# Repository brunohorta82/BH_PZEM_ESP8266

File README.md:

# BH PZEM

**Conteúdo **   
1. [Intro](#id1)
2. [Hardware](#id2)
3. [Firmware](https://github.com/brunohorta82/BH-Easy-Iot)
4. [Hack de sentido da corrente](#id4)
5. [Exemplos](#id5)
   - [BH PZEM-004 Wi-Fi](#id6)
5. [Donativos](#id7)

## Intro 

**BH Pzem** é um dispositivo baseado em ESP8266 e PZEM-004 que mede energia e / ou temperatura e enviaos dados a um broker MQTT e / ou Emoncms. O BH Pzem é modular, o que significa que podemos começar com um simples módulo de energia até um sistema de monitorização de produção energética, juntamente com detecção de temperatura (até 10 sensores de temperatura digital). Podemos ainda adicionar um diplay Oled e relés.
Os dados são enviados via Wi-Fi

**Painel de Controlo:**

**Medição de Energia:**
  - Baseado no PZEM-004
  - Leituras muito rigorosas 
  - Possibilidade de detecão de sentido de energia 
  - Voltagem, Amperagem, Potência, Energia

**Medição de Temperatura:**
  - Baseado no sensor 1-wire DS18B20
  - Permite adicionar até 10 sensores digitais DS18B20
  - Endereços dos sensores geridos na interface Web

**Relé :**
  - Controlado via MQTT

**ESP8266**:
  - Facilmente configurado na Interface Web
  - Envio dos dados em JSON via MQTT
  - Envio dos dados para um servidor Emoncms local/remoto
  
## Hardware 

Qtd | Item | Imagem
:---: | :---: | ---:
1 | PZEM-004 | `...`
1 | ESP-12E | `...`
1 | PCB BH-PZEM Wi-Fi | `...`
1 | Fonte HLK-PM01 | `...`
1 | Regulador de Tensão AMS1117 3.3v | `...`
1 | Condensador Cerâmico 100nF SMD | `...`
5 | Resistência 10K 0603 | `...`
1 | Resistência 4.7K 0603 | `...`
1 | Resistência 1K 0603 | `...`
1 | Optocopolador PC | `...`
2 | Botão 3*4*2 MM SMD | `...`
1 | Fusível T2A 2A 250 | `...`
1 | Sensor temperatua DS18B20 | `...`
1 | Terminal de Parafuso 2P 5.0mm  | `...`
2 | Terminal 2P 2.54mm  | `...`
1 | Conector de 9 Pinos Fêmea 2.54mm | `...`
1 | Conector de 8 Pinos Fêmea 2.54mm | `...`
1 | Conector de 4 Pinos Macho 2.54mm | `...`
1 | Conector de 7 Pinos Macho 2.54mm | `...`

## Software 

- Arduino Ide
- Editar o ficheiro config.h com o setup inicial
- Upload do Firmware para o ESP8266
- Aceder ao AP `SSID:BH_PZEM_NODE_ID` e configurar a Rede Wi-Fi
- Navegar até  `http://<bh-pzem name>.local` ou `http://<bh-pzem IP address>`
- Verificar o sentido da corrente caso tenham feito o Hack para a deteção
- Configurar o `MQTT broker` e/ou a conta do `Emoncms` 
- E tá feito, agora é só curtir :) 

## Hack para deteção de sentido de corrente 

![](https://lh3.googleusercontent.com/7oKvPvdqY3lP6zBprZ33XxJ7tKCSPjcxN2w-OqwHl_1SzNu80wvdnXQUsuom1qUd44zljcSAKoW6R_QD6Fw6dyNdrQpZGyCAt7fK76CRAaeEPu2qT8z-xMeqMLAlgMNtwaDBF7miqPXhsgoQ-rWaterlj8KB61w-i8nbBX3sqG_NviRIJFRPZu4y5Mk5QQHA83q366xY_NipzpD8CfSDKwin57H3Htds_hMZ-07q1bP9mxqiQBRQqcq6nFyu7SyfzQPI7FPg7txX6qM7KTZdOb53coQP14PXP9ZpZgZd6tcLpuRveteLxfdhUHiUXz74R1f_4OeA_25O--yq3BcZT_W89wb5o-ZRAX4VKxyWw7SOmyMhGib1QK7HJxYOTOWC5yf9IasuEWV_vbtsjChd_gD7Al2RD4akmTF-P8RQy6oLgGEKNINEdbHCTc4NhU0PtUVe3b90hhll2i0vlXHoQQ_Dcv1H4UQkiork0te3gWIpN9IEScdoKep3nyKpx4NwDmuup3uilXumtjUWld5qL1ifNlgKCKj39EcPMyswWAbB7pGrEsRqt0L_xvEW9gpEuPkjH6MUEL-biGVslIl6hkCvgLHb1iIcVd2EOjmNMurGXLUkB2KS3h3Vw4LIQRWzvFUrmJfLbP9hZKorvSnoDPO2MfHhwYYeXgx2m2J11w=w800-h402-no)

## Exemplos de BH-PZEM 

### BH PZEM-004 Wi-Fi 

## Caixas e Adaptadores
 - [BHPZEM Suporte DIN Powered by Bruno Horta](https://cad.onshape.com/documents/db83fdb5f2287efd0e4b6ae1/w/3f678a7db5145870a715b4d4/e/e8a96d2384c3348520138283)

## Donativos

Se gostas-te do projeto podes fazer o teu donativo :).

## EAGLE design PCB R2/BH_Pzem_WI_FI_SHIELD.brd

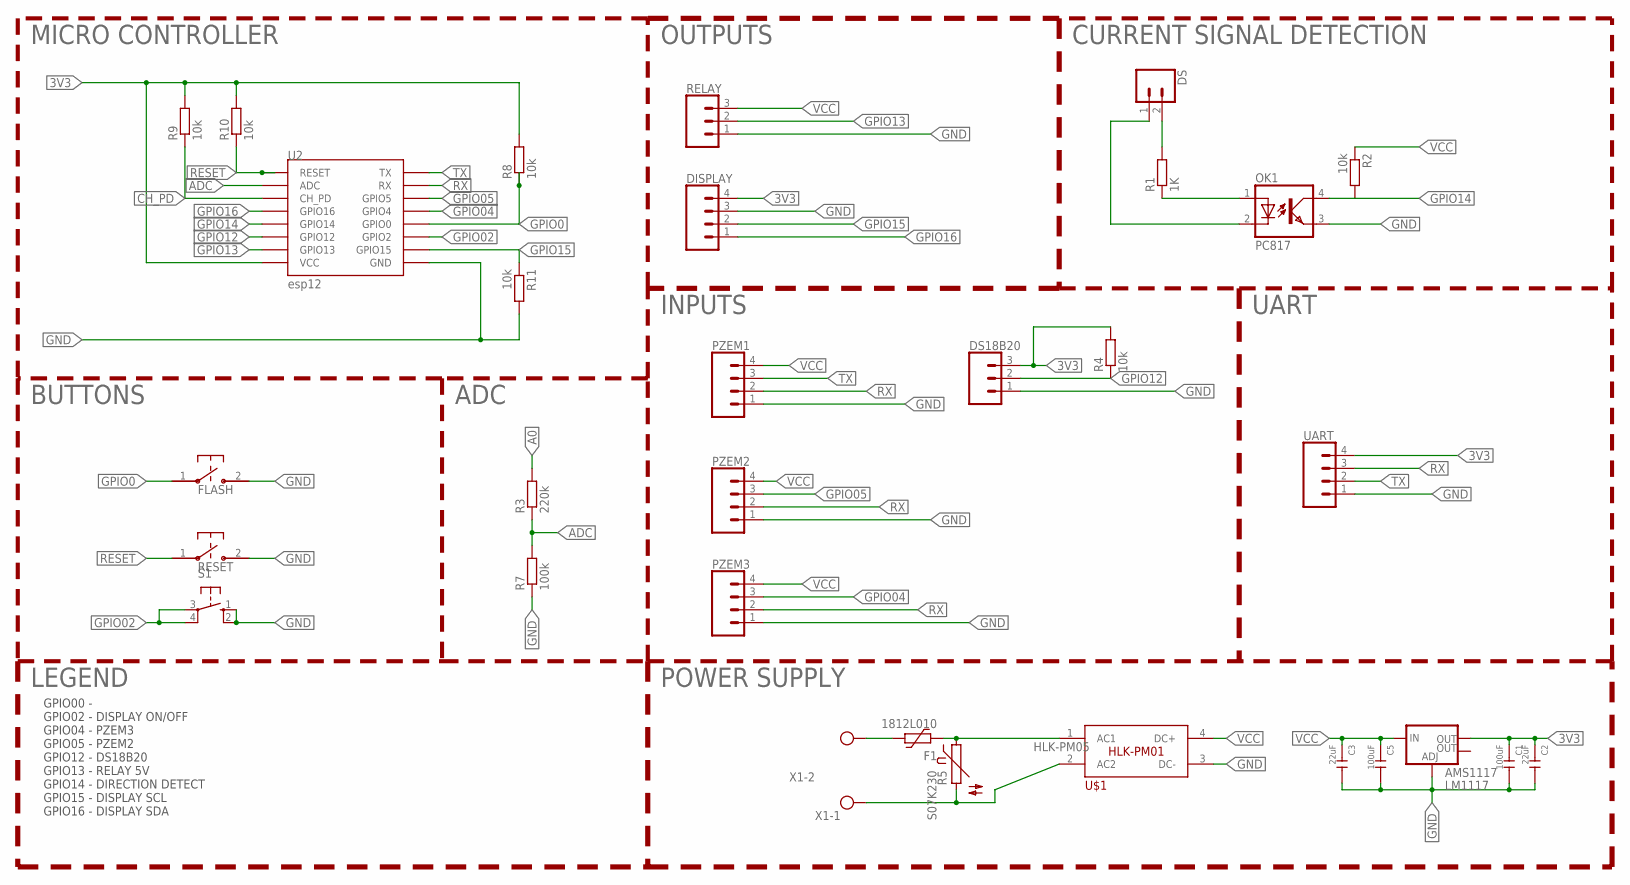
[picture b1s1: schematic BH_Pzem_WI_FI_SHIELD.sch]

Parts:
AMS1117: LM1117; SOT223
C1, C5: 100uF; C1206
C2, C3: 22uF; C1206
DISPLAY: CONN_04JST-PTH-VERT; JST-4-PTH-VERT
DS: CONN_02; 1X02
DS18B20: CONN_03JST-PTH-VERT; JST-3-PTH-VERT
F1: 1812L010; 1812L
FLASH: B3U-1000P-2P-SMD; B3U-1000P
OK1: PC817; DIL04
PZEM1, PZEM2, PZEM3: CONN_04JST-PTH-VERT; JST-4-PTH-VERT
R1: 1K; R0603
R2, R4, R8, R9, R10, R11: 10k; R0603
R3: 220k; R0603
R5: S07K230
R7: 100k; R0603
RELAY: CONN_03JST-PTH-VERT; JST-3-PTH-VERT
RESET: B3U-1000P-2P-SMD; B3U-1000P
S1: 10-XX; B3F-10XX
U2: esp12; ESP12-SMD
U$1: HLK-PM01
UART: CONN_04JST-PTH-VERT; JST-4-PTH-VERT
X1: W237-102

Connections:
3V3: AMS1117.2 (OUT), C1.1, C2.1, DISPLAY.4, DS18B20.3, R4.2, R8.2, R9.2, R10.2, U2.VCC, UART.4
A0: R3.2
ADC: R3.1, R7.2, U2.ADC
CH_PD: R9.1, U2.CH_PD
GND: AMS1117.1 (ADJ), C1.2, C2.2, C3.2, C5.2, DISPLAY.3, DS18B20.1, FLASH.2, OK1.3 (EMIT), PZEM1.1, PZEM2.1, PZEM3.1, R7.1, R11.2, RELAY.1, RESET.2, S1.1 (S), S1.2 (S1), U2.GND, U$1.3 (DC-), UART.1
GPIO0: FLASH.1, R8.1, U2.GPIO0
GPIO02: S1.3, S1.4 (P1), U2.GPIO2
GPIO04: PZEM3.3, U2.GPIO4
GPIO05: PZEM2.3, U2.GPIO5
GPIO12: DS18B20.2, R4.1, U2.GPIO12
GPIO13: RELAY.2, U2.GPIO13
GPIO14: OK1.4 (COL), R2.2, U2.GPIO14
GPIO15: DISPLAY.2, R11.1, U2.GPIO15
GPIO16: DISPLAY.1, U2.GPIO16
LINE_L: F1.2, R5.1, U$1.1 (AC1)
unnamed: OK1.1 (A), R1.1
unnamed: F1.1, X1.2
unnamed: DS.2, R1.2
NEUTRAL_IN: R5.2, U$1.2 (AC2), X1.1
RESET: R10.1, RESET.1, U2.RESET
RX: PZEM1.2, PZEM2.2, PZEM3.2, U2.RXD0 (RX), UART.3
SIGNAL_GND: DS.1, OK1.2 (C)
TX: PZEM1.3, U2.TXD0 (TX), UART.2
VCC: AMS1117.3 (IN), C3.1, C5.1, PZEM1.4, PZEM2.4, PZEM3.4, R2.1, RELAY.3, U$1.4 (DC+)

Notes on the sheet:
CURRENT SIGNAL DETECTION
INPUTS
BUTTONS
MICRO CONTROLLER
HLK-PM05
ADC
OUTPUTS
GPIO00 - GPIO02 - DISPLAY ON/OFF GPIO04 - PZEM3 GPIO05 - PZEM2 GPIO12 - DS18B20 GPIO13 - RELAY 5V GPIO14 - DIRECTION DETECT GPIO15 - DISPLAY SCL GPIO16 - DISPLAY SDA
POWER SUPPLY
LEGEND
UART

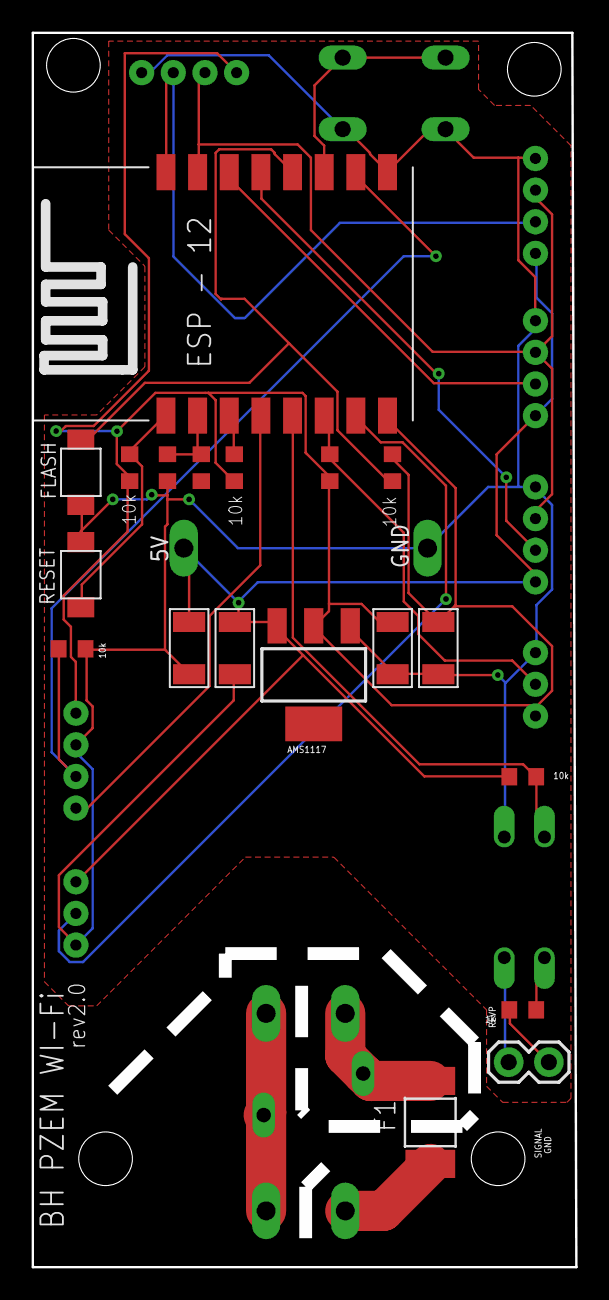
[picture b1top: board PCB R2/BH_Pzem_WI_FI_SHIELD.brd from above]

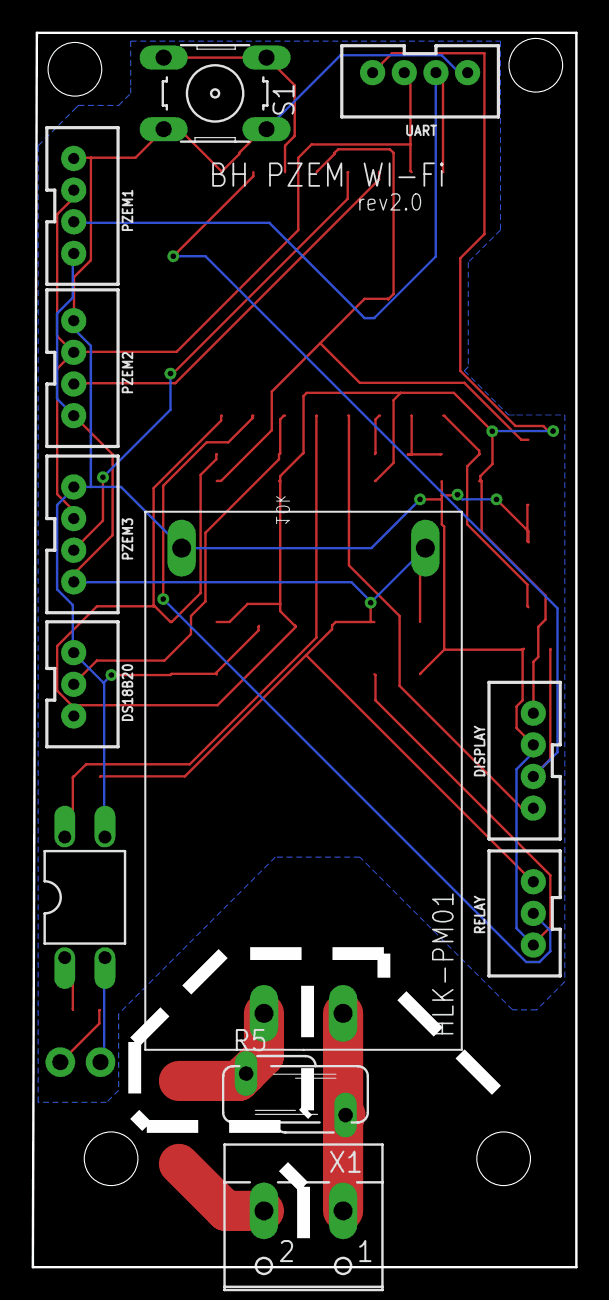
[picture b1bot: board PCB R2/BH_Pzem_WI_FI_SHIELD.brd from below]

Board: 2 copper layers, 33.7 x 77.3 mm, 31 parts (12 on the bottom side), 23 nets.

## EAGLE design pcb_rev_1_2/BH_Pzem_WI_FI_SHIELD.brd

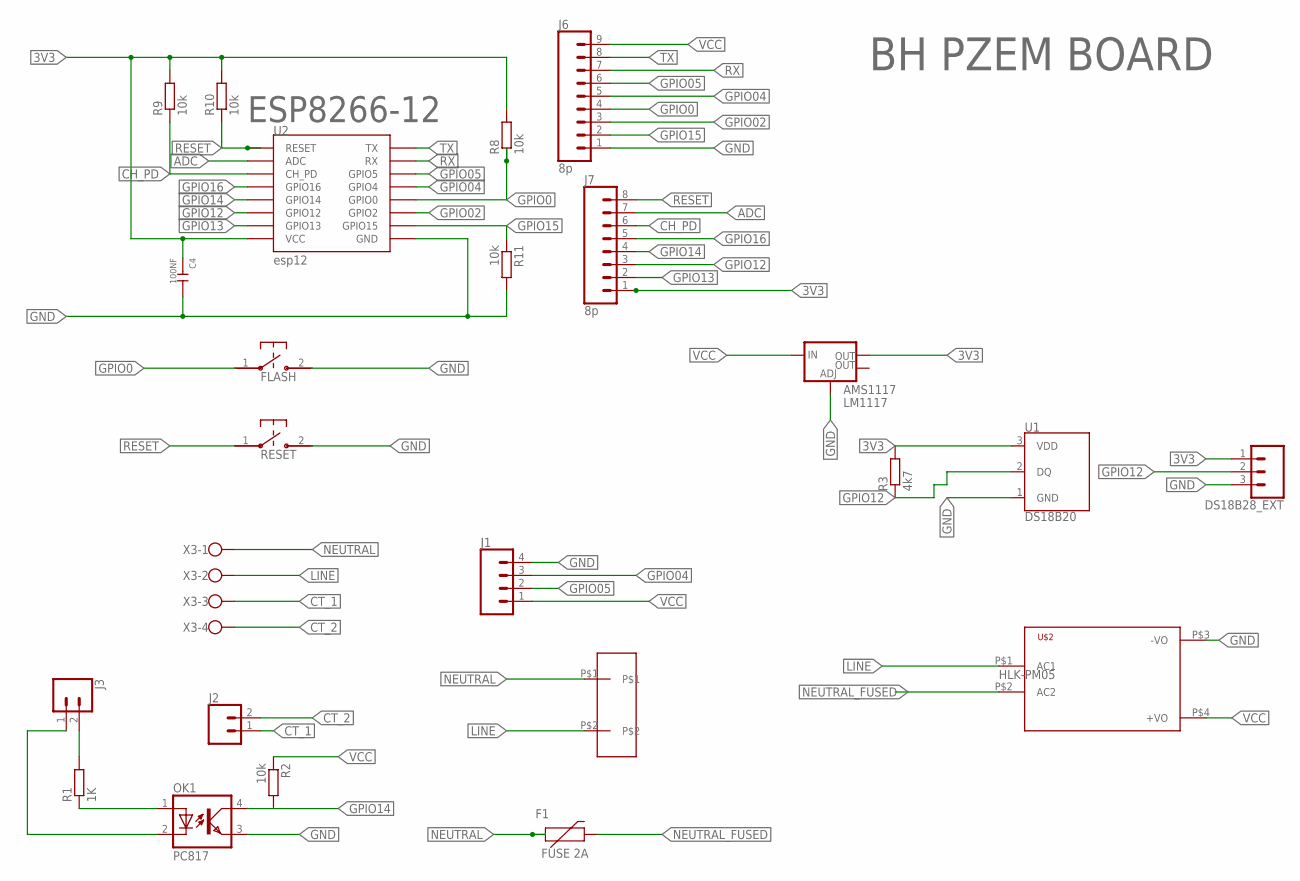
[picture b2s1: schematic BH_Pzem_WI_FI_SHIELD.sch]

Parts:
AMS1117: LM1117; SOT223
C4: 100NF; C1206
DS18B28_EXT: CONN_03; 1X03
F1: FUSE 2A; PTH
FLASH: B3U-1000P-2P-SMD; B3U-1000P
J1: CONN_04; 1X04
J2, J3: CONN_02; 1X02
J6: 8p; 1X09
J7: 8p; 1X08
OK1: PC817; DIL04
R1: 1K; R0603
R2, R8, R9, R10, R11: 10k; R0603
R3: 4k7; R0603
RESET: B3U-1000P-2P-SMD; B3U-1000P
U1: DS18B20; TO-92-AMMO
U2: esp12; ESP12-SMD
U$1: SCREWTERMINALS_5MM_2; TERMINAL_2X
U$2: HKLPM01
X3: W237-4

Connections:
3V3: AMS1117.2 (OUT), C4.1, DS18B28_EXT.1, J7.1, R3.2, R8.2, R9.2, R10.2, U1.3 (VDD), U2.VCC
ADC: J7.7, U2.ADC
CH_PD: J7.6, R9.1, U2.CH_PD
CT_1: J2.1, X3.3
CT_2: J2.2, X3.4
GND: AMS1117.1 (ADJ), C4.2, DS18B28_EXT.3, FLASH.2, J1.4, J6.1, OK1.3 (EMIT), R11.2, RESET.2, U1.1 (GND), U2.GND, U$2.P$3 (-VO)
GPIO0: FLASH.1, J6.4, R8.1, U2.GPIO0
GPIO02: J6.3, U2.GPIO2
GPIO04: J1.3, J6.5, U2.GPIO4
GPIO05: J1.2, J6.6, U2.GPIO5
GPIO12: DS18B28_EXT.2, J7.3, R3.1, U1.2 (DQ), U2.GPIO12
GPIO13: J7.2, U2.GPIO13
GPIO14: J7.4, OK1.4 (COL), R2.2, U2.GPIO14
GPIO15: J6.2, R11.1, U2.GPIO15
GPIO16: J7.5, U2.GPIO16
LINE: U$1.P$2, U$2.P$1 (AC1), X3.2
unnamed: OK1.1 (A), R1.1
unnamed: J3.2, R1.2
NEUTRAL: F1.P$1 (1), U$1.P$1, X3.1
NEUTRAL_FUSED: F1.P$2 (2), U$2.P$2 (AC2)
RESET: J7.8, R10.1, RESET.1, U2.RESET
RX: J6.7, U2.RXD0 (RX)
SIGNAL_GND: J3.1, OK1.2 (C)
TX: J6.8, U2.TXD0 (TX)
VCC: AMS1117.3 (IN), J1.1, J6.9, R2.1, U$2.P$4 (+VO)

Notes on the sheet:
HLK-PM05
BH PZEM BOARD
ESP8266-12

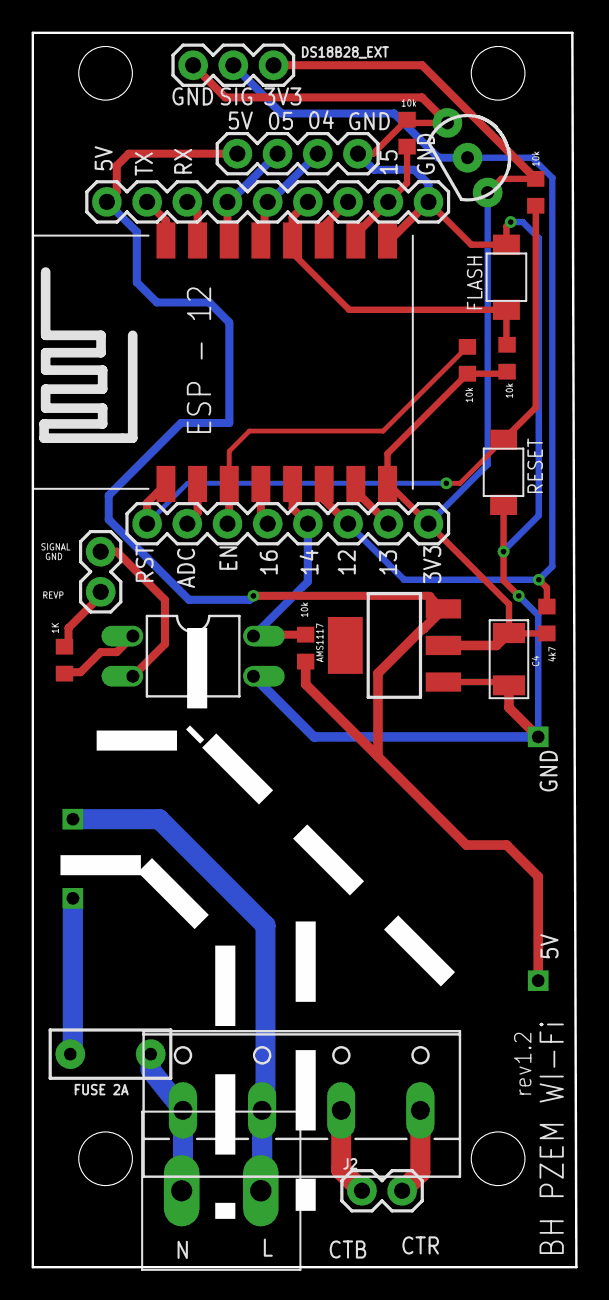
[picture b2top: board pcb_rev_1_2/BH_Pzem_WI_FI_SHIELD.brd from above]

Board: 2 copper layers, 33.2 x 76.9 mm, 24 parts (0 on the bottom side), 25 nets.

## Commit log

2018-03-21 no message
2018-03-21 WI-FI Shield
2018-03-22 pista em falta para o GND
2018-04-02 gerber
2018-04-11 Código melhorado, Board rev1.1 in progress
2018-04-12 rev 1.1 board
2018-04-14 Código para mostrar a temperatura com o sensor dallas ligado ao pino 12
2018-04-19 melhoramento de PCB e de código
2018-04-19 fotos
2018-07-06 foto da pcb
2018-07-08 Webupdate, detecção de sentido de corrente
2018-07-09 Foto atualizada da PCB, optimização de código
2018-07-09 organização de pastas
2018-07-09 webpanel
2018-07-10 web panel
2018-07-11 Painel de configuração
2018-07-11 versão 1.1
2018-07-11 Painel de configuração, detecção dinamica de sensores de temperatura
2018-07-11 suporte para relés
2018-07-11 fix bug on ArduinoJson Lib
2018-07-11 fix bug json, painel novo
2018-07-11 Correcção dos valores estáticos no painel de controlo
2018-07-12 implementação de relés controlados por mqtt
2018-07-12 Update via Painel de Controlo (WEB)
2018-07-12 Update HTML and JS
2018-07-12 Add HTML and JS to static_site and add HOSTNAME field
2018-07-12 Add IOS
2018-07-12 Add IOS to static
2018-07-12 Configuração dinámica de GPIOs, licença MIT
2018-07-12 manometros de medição, bloqueio de espaços no nome do node, melhoramento do painel de controlo
2018-07-12 binário para update
2018-07-12 remoção de antigo binário
2018-07-12 servidor de desenvolvimento local para bh-pzem-esp8266-ui
2018-07-12 fix bug, atualização de Leituras
2018-07-12 novo gauge de consumo total
2018-07-12 limpeza de headers repetidos
2018-07-12 Auto stash before merge of "master" and "origin/master"
2018-07-12 Inclusão do AdminLTE Admin Template
2018-07-12 relés por MQTT, auto criação de switch no homeassistant
2018-07-13 fix scroll bug when gauge update
2018-07-13 split branches
2018-07-13 Minor Changes index`s
2018-07-13 painel de configuração atualizado, mDNS a funcionar
2018-07-13 reiniciar caso a password ou o nome da rede wi-fi seja alterada
2018-07-13 Adicionado task no gulp para criar ficheiro static_site.h automaticamente
2018-07-13 implementação de gestão de wi-fi e reboot de device
2018-07-13 fix admin lte configuration
2018-07-13 optimização no codigo de condiguração
2018-07-13 versao 1.6
2018-07-14 PCB REV 1.2. Melhorias - Pistas de alimentação mais largas - Orifícios de header 250v mais largos - Adicionado um header para extender o numero de sensores de temperatura (DS18b28_ext)
2018-07-14 atualização de foto de pcb
2018-07-14 atualização do screenshot do painel
2018-07-14 Melhoramento das PCB Labels
2018-07-14 [DOCUMENTAÇÃO] - PIN OUT
2018-07-16 Criação de sensores automaticamente no home assistant, display
2018-07-16 Configuração de GPIOS para o Display via WEB
2018-07-16 FIX mqtt topic para o homeassistant
2018-07-17 pinos SDA e SCL para o display configuraveis via Web Panel
2018-07-17 alteração de cores e remoção de markup
2018-07-17 remoção de fontes desnecessárias
2018-07-17 fix bug index2
2018-07-17 update index2
2018-07-17 navegaçõo de menu
2018-07-17 navegação de menu
2018-07-17 update forms
2018-07-17 Auto stash before merge of "dev_lte" and "origin/dev_lte"
2018-07-17 fix merge errors
2018-07-17 Cleanup markup dev files
2018-07-17 Gauge Meter CSS overrides for Admin LTE
2018-07-17 Formulário NÓ
2018-07-17 Formulário WI-FI
2018-07-17 Formulário GPIO's
2018-07-17 Formulário MQTT
2018-07-17 Formulário EMONCMS
2018-07-17 Formulário ACTUALIZAR
2018-07-18 implementação do markup do Andre, reorganização de ficheiros
2018-07-18 Implementação do Novo template no Ide do Arduino
2018-07-18 implementação das fonts e css no IDE do Arduino, testes no ESP8266 OK
2018-07-19 implementação de will topic no mqtt
2018-07-19 protecão de formulários
2018-07-19 Implementação de botões para reset de fábrica e reboot
2018-07-20 Wi-fi status
2018-07-27 Pesquisa de rede wi-fi, janela de logs, estado da ligação
2018-08-04 Redirect on Save e Wi-Fi Scan
2018-08-04 Novo Layout, remoção do configurador de GPIO' Online (será implementado futuramente)
2018-08-09 possibilidade de configuração de porta do EMONCMS
2018-08-31 mqtt topic name fix
2018-09-06 versão 2.3
2018-10-30 display
2018-11-01 Actualização de MQTT
    A temperatura não consigo
2018-11-16 passagem de firmware para Easy Iot
    passagem de firmware para Easy Iot
2018-11-16 PCB Rev.1.2
    Expanção para Sensores de temperatura Dallas OneWire
2018-11-16 docs e caixas
2018-12-13 Wiring Display
    Esquema de Ligação para Display Oled
2018-12-18 rev2.0 progress
2019-01-16 rev2
2019-03-25 Versão 4 Firmware
    melhoramento na estabilidade
2019-04-02 V4 Compativel com App OnOfre
2019-04-05 mqtt homeassist bug
2019-04-05 v4.4
2019-04-05 v4.5
2019-06-18 v6.1

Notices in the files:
parts and their libraries:
SparkFun-Connectors: Licensing: Creative Commons ShareAlike 4.0 International - https://creativecommons.org/licenses/by-sa/4.0
